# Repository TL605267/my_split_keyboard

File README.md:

# my_split_keyboard
My first split keyboard design using CH582F MCU. Key position is based on sofle

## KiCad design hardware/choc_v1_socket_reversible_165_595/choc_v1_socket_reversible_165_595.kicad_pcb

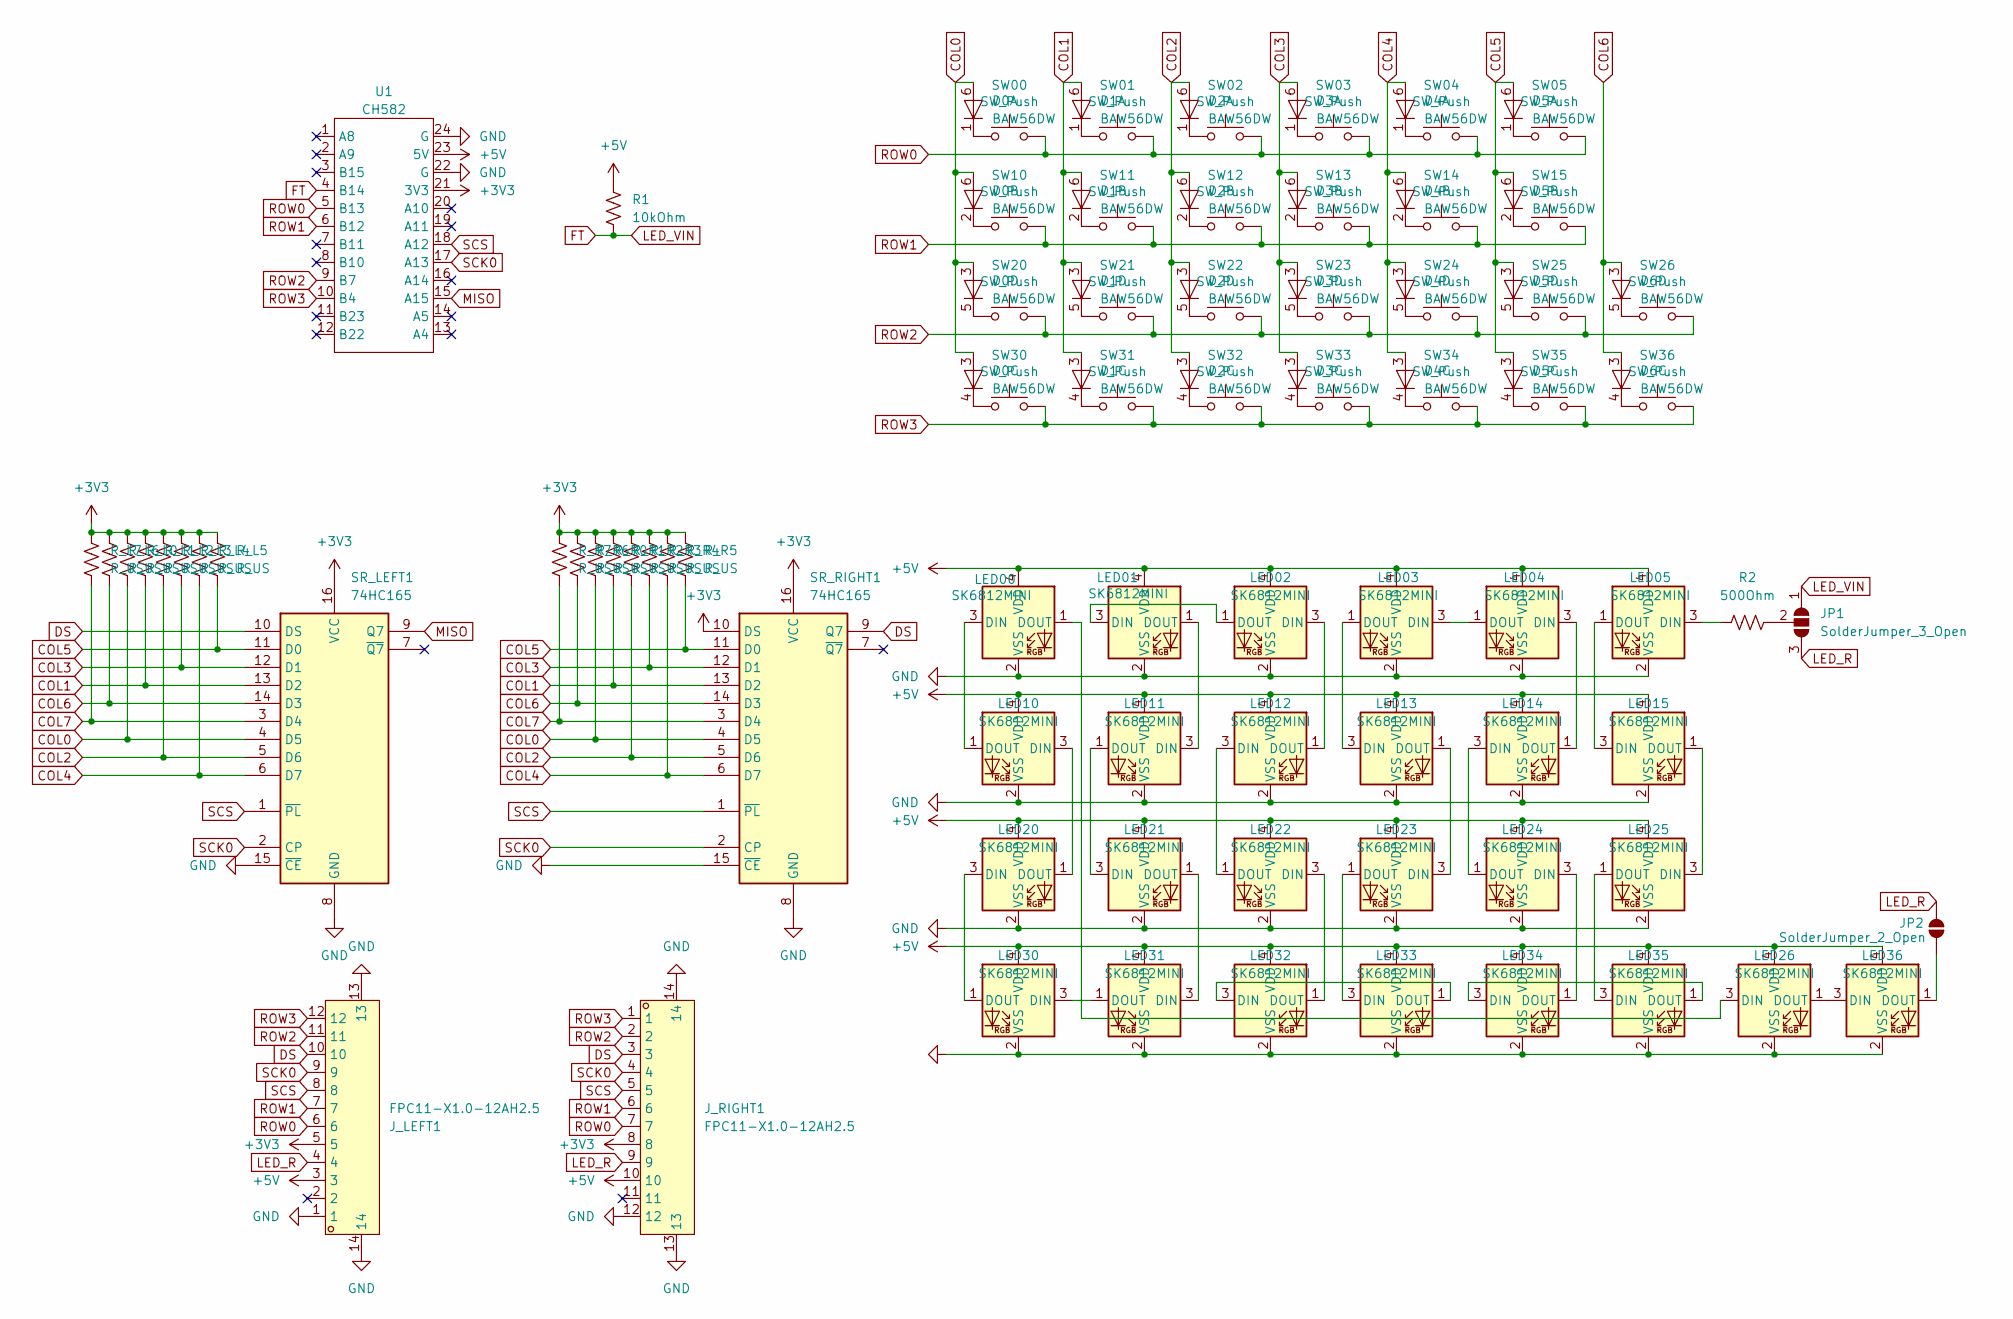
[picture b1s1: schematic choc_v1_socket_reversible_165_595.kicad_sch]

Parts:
D0, D1, D2, D3, D4, D5, D6: BAW56DW; BAW70DW_reversible
JP1: SolderJumper_3_Open; SolderJumper-3_P2.0mm_Open_TrianglePad1.0x1.5mm_NumberLabels
JP2: SolderJumper_2_Open; SolderJumper-2_P1.3mm_Open_TrianglePad1.0x1.5mm
J_LEFT1: FPC11-X1.0-12AH2.5; FPC-SMD_12P-P1.00_XYECONN_FPC10-S1.0-12AH2.5; LCSC Part C19269900
J_RIGHT1: FPC11-X1.0-12AH2.5; FPC-SMD_12P-P1.00_XYECONN_FPC10-S1.0-12AH2.5; LCSC Part C19269900
LED00, LED01, LED02, LED03, LED04, LED05, LED10, LED11, LED12, LED13, LED14, LED15, LED20, LED21, LED22, LED23, LED24, LED25, LED26, LED30, LED31, LED32, LED33, LED34, LED35, LED36: SK6812MINI; LED_SK6812MINI_E_REVERSIBLE
R1: 10kOhm; R_0805_2012Metric
R2: 500Ohm; R_0805_2012Metric
R_L0, R_L1, R_L2, R_L3, R_L4, R_L5, R_L6, R_L7: R_US; R_0805_2012Metric_Pad1.20x1.40mm_HandSolder
R_R0, R_R1, R_R2, R_R3, R_R4, R_R5, R_R6, R_R7: R_US; R_0805_2012Metric_Pad1.20x1.40mm_HandSolder
SR_LEFT1: 74HC165; SOP-16_3.9x9.9mm_P1.27mm
SR_RIGHT1: 74HC165; SOP-16_3.9x9.9mm_P1.27mm
SW00, SW01, SW02, SW03, SW04, SW05, SW10, SW11, SW12, SW13, SW14, SW15, SW20, SW21, SW22, SW23, SW24, SW25, SW26, SW30, SW31, SW32, SW33, SW34, SW35, SW36: SW_Push; Kailh_socket_PG1350_reversible
U1: CH582; DIP-24_W15.24mm

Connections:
+3V3: J_LEFT1.5, J_RIGHT1.8, R_L0.1, R_L1.1, R_L2.1, R_L3.1, R_L4.1, R_L5.1, R_L6.1, R_L7.1, R_R0.1, R_R1.1, R_R2.1, R_R3.1, R_R4.1, R_R5.1, R_R6.1, R_R7.1, SR_LEFT1.16 (VCC), SR_RIGHT1.10 (DS), SR_RIGHT1.16 (VCC), U1.21 (3V3)
+5V: J_LEFT1.3, J_RIGHT1.10, LED00.4 (VDD), LED01.4 (VDD), LED02.4 (VDD), LED03.4 (VDD), LED04.4 (VDD), LED05.4 (VDD), LED10.4 (VDD), LED11.4 (VDD), LED12.4 (VDD), LED13.4 (VDD), LED14.4 (VDD), LED15.4 (VDD), LED20.4 (VDD), LED21.4 (VDD), LED22.4 (VDD), LED23.4 (VDD), LED24.4 (VDD), LED25.4 (VDD), LED26.4 (VDD), LED30.4 (VDD), LED31.4 (VDD), LED32.4 (VDD), LED33.4 (VDD), LED34.4 (VDD), LED35.4 (VDD), LED36.4 (VDD), R1.1, U1.23 (5V)
COL0: D0.3 (A), D0.6 (A), R_L0.2, R_R0.2, SR_LEFT1.4 (D5), SR_RIGHT1.4 (D5)
COL1: D1.3 (A), D1.6 (A), R_L1.2, R_R1.2, SR_LEFT1.13 (D2), SR_RIGHT1.13 (D2)
COL2: D2.3 (A), D2.6 (A), R_L2.2, R_R2.2, SR_LEFT1.5 (D6), SR_RIGHT1.5 (D6)
COL3: D3.3 (A), D3.6 (A), R_L3.2, R_R3.2, SR_LEFT1.12 (D1), SR_RIGHT1.12 (D1)
COL4: D4.3 (A), D4.6 (A), R_L4.2, R_R4.2, SR_LEFT1.6 (D7), SR_RIGHT1.6 (D7)
COL5: D5.3 (A), D5.6 (A), R_L5.2, R_R5.2, SR_LEFT1.11 (D0), SR_RIGHT1.11 (D0)
COL6: D6.3 (A), R_L6.2, R_R6.2, SR_LEFT1.14 (D3), SR_RIGHT1.14 (D3)
COL7: R_L7.2, R_R7.2, SR_LEFT1.3 (D4), SR_RIGHT1.3 (D4)
DS: J_LEFT1.10, J_RIGHT1.3, SR_LEFT1.10 (DS), SR_RIGHT1.9 (Q7)
FT: JP1.1 (A), R1.2, U1.4 (B14)
GND: J_LEFT1.1, J_LEFT1.13, J_LEFT1.14, J_RIGHT1.12, J_RIGHT1.13, J_RIGHT1.14, LED00.2 (VSS), LED01.2 (VSS), LED02.2 (VSS), LED03.2 (VSS), LED04.2 (VSS), LED05.2 (VSS), LED10.2 (VSS), LED11.2 (VSS), LED12.2 (VSS), LED13.2 (VSS), LED14.2 (VSS), LED15.2 (VSS), LED20.2 (VSS), LED21.2 (VSS), LED22.2 (VSS), LED23.2 (VSS), LED24.2 (VSS), LED25.2 (VSS), LED26.2 (VSS), LED30.2 (VSS), LED31.2 (VSS), LED32.2 (VSS), LED33.2 (VSS), LED34.2 (VSS), LED35.2 (VSS), LED36.2 (VSS), SR_LEFT1.8 (GND), SR_LEFT1.15 (~CE), SR_RIGHT1.8 (GND), SR_RIGHT1.15 (~CE), U1.22 (G), U1.24 (G)
LED_R: JP1.3 (B), JP2.2 (B), J_LEFT1.4, J_RIGHT1.9
MISO: SR_LEFT1.9 (Q7), U1.15 (A15)
unnamed: D0.1 (K), SW00.1
unnamed: D0.2 (K), SW10.1
unnamed: D0.4 (K), SW30.1
unnamed: D0.5 (K), SW20.1
unnamed: D1.1 (K), SW01.1
unnamed: D1.2 (K), SW11.1
unnamed: D1.4 (K), SW31.1
unnamed: D1.5 (K), SW21.1
unnamed: D2.1 (K), SW02.1
unnamed: D2.2 (K), SW12.1
unnamed: D2.4 (K), SW32.1
unnamed: D2.5 (K), SW22.1
unnamed: D3.1 (K), SW03.1
unnamed: D3.2 (K), SW13.1
unnamed: D3.4 (K), SW33.1
unnamed: D3.5 (K), SW23.1
unnamed: D4.1 (K), SW04.1
unnamed: D4.2 (K), SW14.1
unnamed: D4.4 (K), SW34.1
unnamed: D4.5 (K), SW24.1
unnamed: D5.1 (K), SW05.1
unnamed: D5.2 (K), SW15.1
unnamed: D5.4 (K), SW35.1
unnamed: D5.5 (K), SW25.1
unnamed: D6.4 (K), SW36.1
unnamed: D6.5 (K), SW26.1
unnamed: JP1.2 (C), R2.2
unnamed: JP2.1 (A), LED36.1 (DOUT)
unnamed: LED00.3 (DIN), LED10.1 (DOUT)
unnamed: LED00.1 (DOUT), LED26.3 (DIN)
unnamed: LED01.3 (DIN), LED02.1 (DOUT)
unnamed: LED01.1 (DOUT), LED11.3 (DIN)
unnamed: LED02.3 (DIN), LED12.1 (DOUT)
unnamed: LED03.3 (DIN), LED04.1 (DOUT)
unnamed: LED03.1 (DOUT), LED13.3 (DIN)
unnamed: LED04.3 (DIN), LED14.1 (DOUT)
unnamed: LED05.3 (DIN), R2.1
unnamed: LED05.1 (DOUT), LED15.3 (DIN)
unnamed: LED10.3 (DIN), LED20.1 (DOUT)
unnamed: LED11.1 (DOUT), LED21.3 (DIN)
unnamed: LED12.3 (DIN), LED22.1 (DOUT)
unnamed: LED13.1 (DOUT), LED23.3 (DIN)
unnamed: LED14.3 (DIN), LED24.1 (DOUT)
unnamed: LED15.1 (DOUT), LED25.3 (DIN)
unnamed: LED20.3 (DIN), LED30.1 (DOUT)
unnamed: LED21.1 (DOUT), LED31.3 (DIN)
unnamed: LED22.3 (DIN), LED32.1 (DOUT)
unnamed: LED23.1 (DOUT), LED33.3 (DIN)
unnamed: LED24.3 (DIN), LED34.1 (DOUT)
unnamed: LED25.1 (DOUT), LED35.3 (DIN)
unnamed: LED26.1 (DOUT), LED36.3 (DIN)
unnamed: LED30.3 (DIN), LED31.1 (DOUT)
unnamed: LED32.3 (DIN), LED33.1 (DOUT)
unnamed: LED34.3 (DIN), LED35.1 (DOUT)
ROW0: J_LEFT1.6, J_RIGHT1.7, SW00.2, SW01.2, SW02.2, SW03.2, SW04.2, SW05.2, U1.5 (B13)
ROW1: J_LEFT1.7, J_RIGHT1.6, SW10.2, SW11.2, SW12.2, SW13.2, SW14.2, SW15.2, U1.6 (B12)
ROW2: J_LEFT1.11, J_RIGHT1.2, SW20.2, SW21.2, SW22.2, SW23.2, SW24.2, SW25.2, SW26.2, U1.9 (B7)
ROW3: J_LEFT1.12, J_RIGHT1.1, SW30.2, SW31.2, SW32.2, SW33.2, SW34.2, SW35.2, SW36.2, U1.10 (B4)
SCK0: J_LEFT1.9, J_RIGHT1.4, SR_LEFT1.2 (CP), SR_RIGHT1.2 (CP), U1.17 (A13)
SCS: J_LEFT1.8, J_RIGHT1.5, SR_LEFT1.1 (~PL), SR_RIGHT1.1 (~PL), U1.18 (A12)

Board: 2 copper layers, 84 parts (0 on the bottom side), 75 nets, no tracks yet.

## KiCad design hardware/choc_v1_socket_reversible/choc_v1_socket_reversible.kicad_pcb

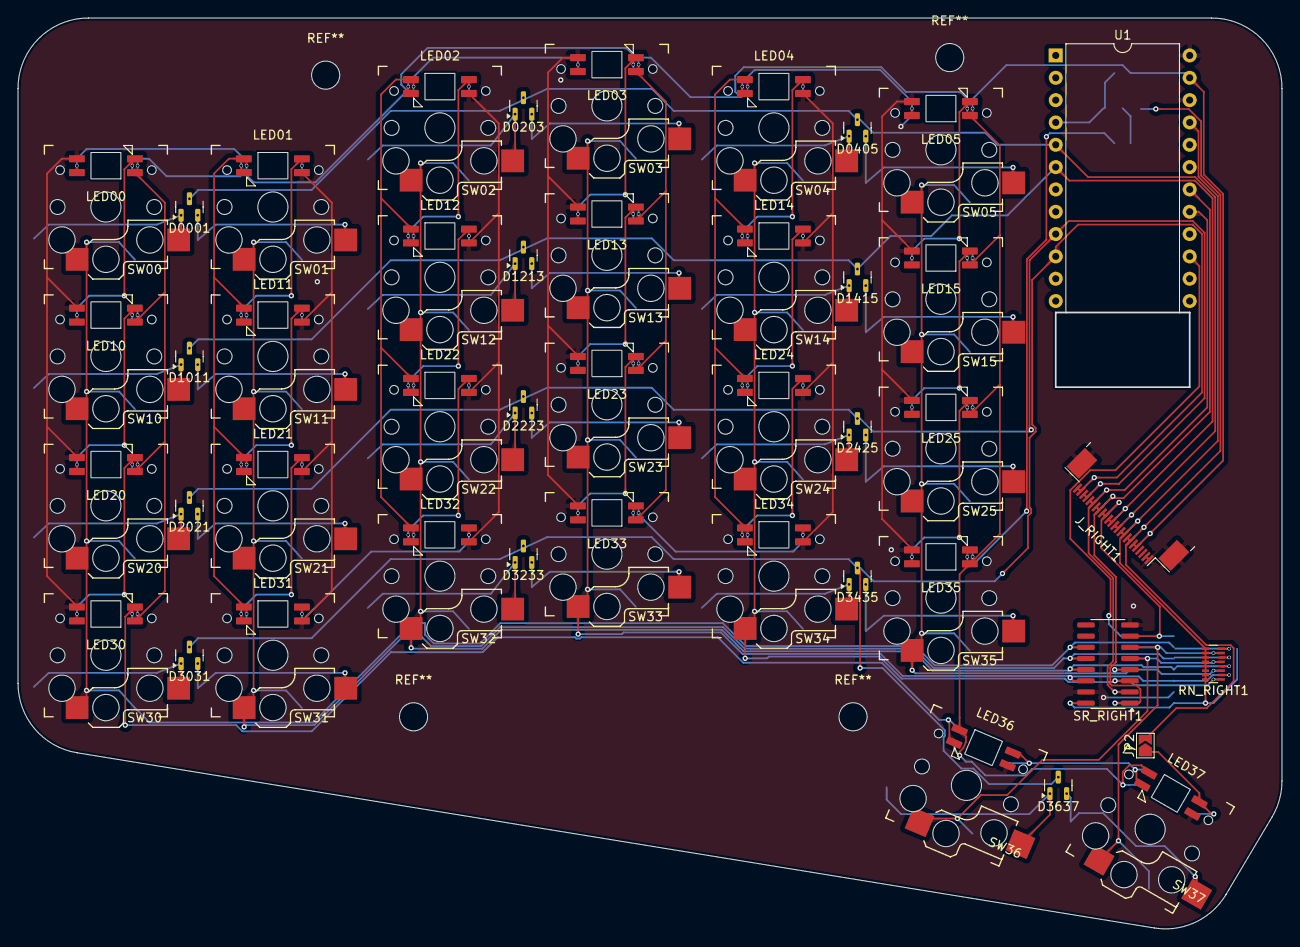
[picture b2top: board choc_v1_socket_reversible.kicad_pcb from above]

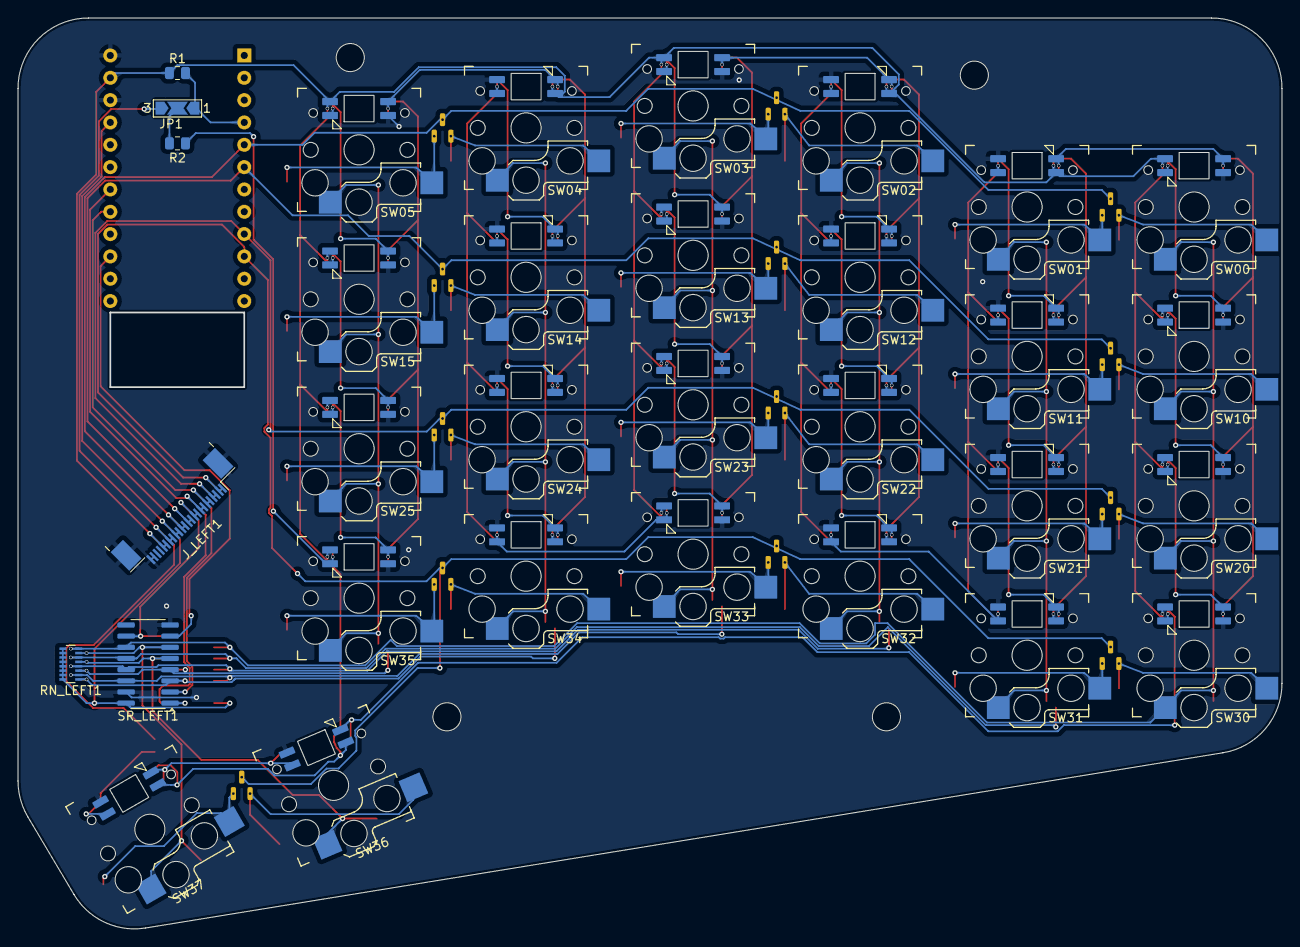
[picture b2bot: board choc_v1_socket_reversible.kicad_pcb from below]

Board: 2 copper layers, 143.7 x 103.5 mm, 76 parts (6 on the bottom side), 75 nets.

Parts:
D0001, D0203, D0405, D1011, D1213, D1415, D2021, D2223, D2425, D3031, D3233, D3435, D3637: BAV70; BAV70_SOT-23_Reversible
JP1: SolderJumper_3_Open; SolderJumper-3_P2.0mm_Open_TrianglePad1.0x1.5mm_NumberLabels
JP2: SolderJumper_2_Open; SolderJumper-2_P1.3mm_Open_TrianglePad1.0x1.5mm
J_LEFT1: Conn_02x12_Odd_Even_MountingPin; Jushuo_AFC07-S24FCA-00_1x24-1MP_P0.50_Horizontal
J_RIGHT1: Conn_02x12_Odd_Even_MountingPin; Jushuo_AFC07-S24FCA-00_1x24-1MP_P0.50_Horizontal
LED00, LED01, LED02, LED03, LED04, LED05, LED10, LED11, LED12, LED13, LED14, LED15, LED20, LED21, LED22, LED23, LED24, LED25, LED30, LED31, LED32, LED33, LED34, LED35, LED36, LED37: SK6812MINI; LED_SK6812MINI_E_REVERSIBLE_1
R1: 10kOhm; R_0805_2012Metric
R2: 500Ohm; R_0805_2012Metric
RN_LEFT1: R_Pack08; R_Array_Convex_8x0602
RN_RIGHT1: R_Pack08; R_Array_Convex_8x0602
SR_LEFT1: 74HC165; SOP-16_3.9x9.9mm_P1.27mm
SR_RIGHT1: 74HC165; SOP-16_3.9x9.9mm_P1.27mm
SW00, SW01, SW02, SW03, SW04, SW05, SW10, SW11, SW12, SW13, SW14, SW15, SW20, SW21, SW22, SW23, SW24, SW25, SW30, SW31, SW32, SW33, SW34, SW35, SW36, SW37: SW_Push; Kailh_socket_PG1350_reversible
U1: CH582; DIP-24_W15.24mm

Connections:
+3V3: J_LEFT1.15, J_LEFT1.16, J_RIGHT1.9, J_RIGHT1.10, RN_LEFT1.9 (R8.2), RN_LEFT1.10 (R7.2), RN_LEFT1.11 (R6.2), RN_LEFT1.12 (R5.2), RN_LEFT1.13 (R4.2), RN_LEFT1.14 (R3.2), RN_LEFT1.15 (R2.2), RN_LEFT1.16 (R1.2), RN_RIGHT1.9 (R8.2), RN_RIGHT1.10 (R7.2), RN_RIGHT1.11 (R6.2), RN_RIGHT1.12 (R5.2), RN_RIGHT1.13 (R4.2), RN_RIGHT1.14 (R3.2), RN_RIGHT1.15 (R2.2), RN_RIGHT1.16 (R1.2), SR_LEFT1.16 (VCC), SR_RIGHT1.16 (VCC), U1.21 (3V3)
+5V: J_LEFT1.19, J_LEFT1.20, J_RIGHT1.5, J_RIGHT1.6, LED00.4 (VDD), LED01.4 (VDD), LED02.4 (VDD), LED03.4 (VDD), LED04.4 (VDD), LED05.4 (VDD), LED10.4 (VDD), LED11.4 (VDD), LED12.4 (VDD), LED13.4 (VDD), LED14.4 (VDD), LED15.4 (VDD), LED20.4 (VDD), LED21.4 (VDD), LED22.4 (VDD), LED23.4 (VDD), LED24.4 (VDD), LED25.4 (VDD), LED30.4 (VDD), LED31.4 (VDD), LED32.4 (VDD), LED33.4 (VDD), LED34.4 (VDD), LED35.4 (VDD), LED36.4 (VDD), LED37.4 (VDD), R1.1, U1.23 (5V)
COL0: RN_LEFT1.8 (R8.1), RN_RIGHT1.8 (R8.1), SR_LEFT1.11 (D0), SR_RIGHT1.11 (D0), SW00.1, SW10.1, SW20.1, SW30.1
COL1: RN_LEFT1.6 (R6.1), RN_RIGHT1.6 (R6.1), SR_LEFT1.12 (D1), SR_RIGHT1.12 (D1), SW01.1, SW11.1, SW21.1, SW31.1
COL2: RN_LEFT1.4 (R4.1), RN_RIGHT1.4 (R4.1), SR_LEFT1.13 (D2), SR_RIGHT1.13 (D2), SW02.1, SW12.1, SW22.1, SW32.1
COL3: RN_LEFT1.2 (R2.1), RN_RIGHT1.2 (R2.1), SR_LEFT1.14 (D3), SR_RIGHT1.14 (D3), SW03.1, SW13.1, SW23.1, SW33.1
COL4: RN_LEFT1.1 (R1.1), RN_RIGHT1.1 (R1.1), SR_LEFT1.3 (D4), SR_RIGHT1.3 (D4), SW04.1, SW14.1, SW24.1, SW34.1
COL5: RN_LEFT1.3 (R3.1), RN_RIGHT1.3 (R3.1), SR_LEFT1.4 (D5), SR_RIGHT1.4 (D5), SW05.1, SW15.1, SW25.1, SW35.1
COL6: RN_LEFT1.5 (R5.1), RN_RIGHT1.5 (R5.1), SR_LEFT1.5 (D6), SR_RIGHT1.5 (D6), SW36.1
COL7: RN_LEFT1.7 (R7.1), RN_RIGHT1.7 (R7.1), SR_LEFT1.6 (D7), SR_RIGHT1.6 (D7), SW37.1
DS: J_LEFT1.9, J_LEFT1.10, J_RIGHT1.15, J_RIGHT1.16, SR_LEFT1.10 (DS), SR_RIGHT1.7 (~Q7)
FT: JP1.1 (A), R1.2, U1.4 (B14)
GND: J_LEFT1.23, J_LEFT1.24, J_LEFT1.MP (MountPin), J_RIGHT1.1, J_RIGHT1.2, J_RIGHT1.MP (MountPin), LED00.2 (VSS), LED01.2 (VSS), LED02.2 (VSS), LED03.2 (VSS), LED04.2 (VSS), LED05.2 (VSS), LED10.2 (VSS), LED11.2 (VSS), LED12.2 (VSS), LED13.2 (VSS), LED14.2 (VSS), LED15.2 (VSS), LED20.2 (VSS), LED21.2 (VSS), LED22.2 (VSS), LED23.2 (VSS), LED24.2 (VSS), LED25.2 (VSS), LED30.2 (VSS), LED31.2 (VSS), LED32.2 (VSS), LED33.2 (VSS), LED34.2 (VSS), LED35.2 (VSS), LED36.2 (VSS), LED37.2 (VSS), SR_LEFT1.8 (GND), SR_LEFT1.15 (~CE), SR_RIGHT1.8 (GND), SR_RIGHT1.15 (~CE), U1.22 (G), U1.24 (G)
LED_R: JP1.3 (B), JP2.2 (B), J_LEFT1.17, J_LEFT1.18, J_RIGHT1.7, J_RIGHT1.8
MISO: SR_LEFT1.7 (~Q7), U1.15 (A15)
unnamed: D0001.1 (A), SW00.2
unnamed: D0001.2 (A), SW01.2
unnamed: D0203.1 (A), SW02.2
unnamed: D0203.2 (A), SW03.2
unnamed: D0405.1 (A), SW04.2
unnamed: D0405.2 (A), SW05.2
unnamed: D1011.1 (A), SW10.2
unnamed: D1011.2 (A), SW11.2
unnamed: D1213.1 (A), SW12.2
unnamed: D1213.2 (A), SW13.2
unnamed: D1415.1 (A), SW14.2
unnamed: D1415.2 (A), SW15.2
unnamed: D2021.1 (A), SW20.2
unnamed: D2021.2 (A), SW21.2
unnamed: D2223.1 (A), SW22.2
unnamed: D2223.2 (A), SW23.2
unnamed: D2425.1 (A), SW24.2
unnamed: D2425.2 (A), SW25.2
unnamed: D3031.1 (A), SW30.2
unnamed: D3031.2 (A), SW31.2
unnamed: D3233.1 (A), SW32.2
unnamed: D3233.2 (A), SW33.2
unnamed: D3435.1 (A), SW34.2
unnamed: D3435.2 (A), SW35.2
unnamed: D3637.1 (A), SW36.2
unnamed: D3637.2 (A), SW37.2
unnamed: JP1.2 (C), R2.2
unnamed: JP2.1 (A), LED37.1 (DOUT)
unnamed: LED00.3 (DIN), LED10.1 (DOUT)
unnamed: LED00.1 (DOUT), LED01.3 (DIN)
unnamed: LED01.1 (DOUT), LED11.3 (DIN)
unnamed: LED02.3 (DIN), LED03.1 (DOUT)
unnamed: LED02.1 (DOUT), LED12.3 (DIN)
unnamed: LED03.3 (DIN), LED13.1 (DOUT)
unnamed: LED04.3 (DIN), LED05.1 (DOUT)
unnamed: LED04.1 (DOUT), LED14.3 (DIN)
unnamed: LED05.3 (DIN), LED15.1 (DOUT)
unnamed: LED10.3 (DIN), LED20.1 (DOUT)
unnamed: LED11.1 (DOUT), LED21.3 (DIN)
unnamed: LED12.1 (DOUT), LED22.3 (DIN)
unnamed: LED13.3 (DIN), LED23.1 (DOUT)
unnamed: LED14.1 (DOUT), LED24.3 (DIN)
unnamed: LED15.3 (DIN), LED25.1 (DOUT)
unnamed: LED20.3 (DIN), LED30.1 (DOUT)
unnamed: LED21.1 (DOUT), LED31.3 (DIN)
unnamed: LED22.1 (DOUT), LED32.3 (DIN)
unnamed: LED23.3 (DIN), LED33.1 (DOUT)
unnamed: LED24.1 (DOUT), LED34.3 (DIN)
unnamed: LED25.3 (DIN), LED35.1 (DOUT)
unnamed: LED30.3 (DIN), LED36.3 (DIN)
unnamed: LED31.1 (DOUT), LED32.1 (DOUT)
unnamed: LED33.3 (DIN), LED34.1 (DOUT)
unnamed: LED35.3 (DIN), R2.1
unnamed: LED36.1 (DOUT), LED37.3 (DIN)
ROW0: D0001.3 (K), D0203.3 (K), D0405.3 (K), J_LEFT1.13, J_LEFT1.14, J_RIGHT1.11, J_RIGHT1.12, U1.5 (B13)
ROW1: D1011.3 (K), D1213.3 (K), D1415.3 (K), J_LEFT1.11, J_LEFT1.12, J_RIGHT1.13, J_RIGHT1.14, U1.6 (B12)
ROW2: D2021.3 (K), D2223.3 (K), D2425.3 (K), J_LEFT1.3, J_LEFT1.4, J_RIGHT1.21, J_RIGHT1.22, U1.9 (B7)
ROW3: D3031.3 (K), D3233.3 (K), D3435.3 (K), D3637.3 (K), J_LEFT1.1, J_LEFT1.2, J_RIGHT1.23, J_RIGHT1.24, U1.10 (B4)
SCK0: J_LEFT1.5, J_LEFT1.6, J_RIGHT1.19, J_RIGHT1.20, SR_LEFT1.2 (CP), SR_RIGHT1.2 (CP), U1.17 (A13)
SCS: J_LEFT1.7, J_LEFT1.8, J_RIGHT1.17, J_RIGHT1.18, SR_LEFT1.1 (~PL), SR_RIGHT1.1 (~PL), U1.18 (A12)

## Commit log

2025-01-25 Added PCB
2025-01-25 Added python script for placing switches in pcbnew
2025-01-26 Fixed row2 and row3 pin connections and added gerber files
2025-01-26 Replaced SIP resistor with 0602x8
2025-02-04 Rotated connector 45 deg, improved routing and optimized vias
2025-02-08 Updated design and python script
2025-02-08 Updated python script so it can be used as plugin; Updated connect_row()
2025-02-09 Added routing for leds. Still need to fix the GND routing
2025-02-09 Fixed led GND routing and rotated texts to correct orientation
2025-02-10 Fixed led routing and din-dout routing
2025-02-10 Replace add_track with add_tracks
2025-02-10 Cleaning up and optimization
2025-02-10 Updated schematic and layout, todo: thumb cluster & MCU place and route
2025-02-10 Updated reference
2025-02-10 Clean up
2025-02-11 Added comments and cleaned up
2025-02-11 Replaced footprint list with dict of ref for faster access; TODO: place & route for thumb cluster, SR and MCU
2025-02-13 Removed redundant vias of GND net, cleaned up thumb clunster tracks
2025-02-13 Placed edge cut, jumper and resistors
2025-02-14 Fixed via placement for connector; TODO: Fix copper pour
2025-02-14 Connected everything and added copper pour
2025-02-14 Improved copper pour
2025-02-15 Generated gerber
2025-02-16 Added mounting hole and antenna cutout
2025-02-20 Cleaned up footprint library, added new design, updated python script
2025-02-21 Improved switch and led routing, cleaned up script
2025-02-21 Fixed diode-sw routing
2025-02-21 Improved shift register - column routing
2025-02-21 Simplified place_via_for_diode
2025-02-22 Cleaning up and refactoring fp_dict
2025-02-22 Replaced dict with dataclass to store footprint info; Cleaned up some functions
2025-02-22 Cleaned up connector placement functions
2025-02-22 Added routing for shift register and resistor
2025-02-22 Added vias for GND/3V3 pins of shift register
2025-02-24 Added python script to convert kicad-generated paste svg file to vinyl cutter svg file
2025-02-24 Implemented same logic using FSM
2025-02-24 Found bug
2025-02-24 Reverted to 47d0de9
2025-02-24 Removed INIT state for better readibility
2025-02-24 Replace group style instead of adding style class
2025-02-26 Added copper pour
2025-02-26 Added filler statements for copper pour
2025-03-25 Switched from dataclass back to dict; Added connection from jumper to MCU
2025-03-25 Added routing for LED_R
2025-04-02 Finished layout
2025-04-02 Updated schematic to use 0805 ressitor and 1x12 FFC socket
2025-04-03 Updated connector and resistor for easier SMD soldering
2025-04-03 Added back connect_sw_col
2025-04-03 Fixed connect_shift_register_and_resistor
2025-04-04 Fixed SER-QH connection
2025-04-05 Firmware initial commit
2025-04-05 Fixed Q7-SER connection
2025-04-12 Added connect_led_5v
2025-04-12 Added connect_rows
